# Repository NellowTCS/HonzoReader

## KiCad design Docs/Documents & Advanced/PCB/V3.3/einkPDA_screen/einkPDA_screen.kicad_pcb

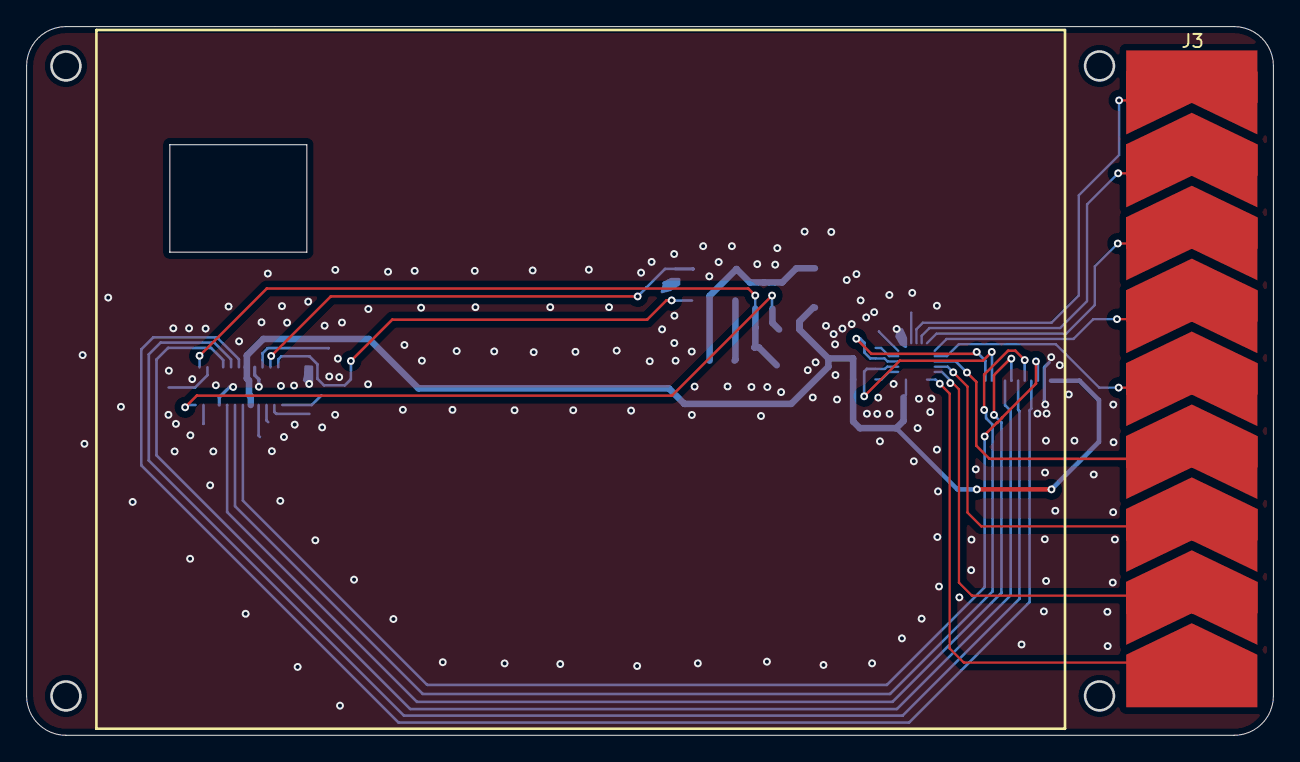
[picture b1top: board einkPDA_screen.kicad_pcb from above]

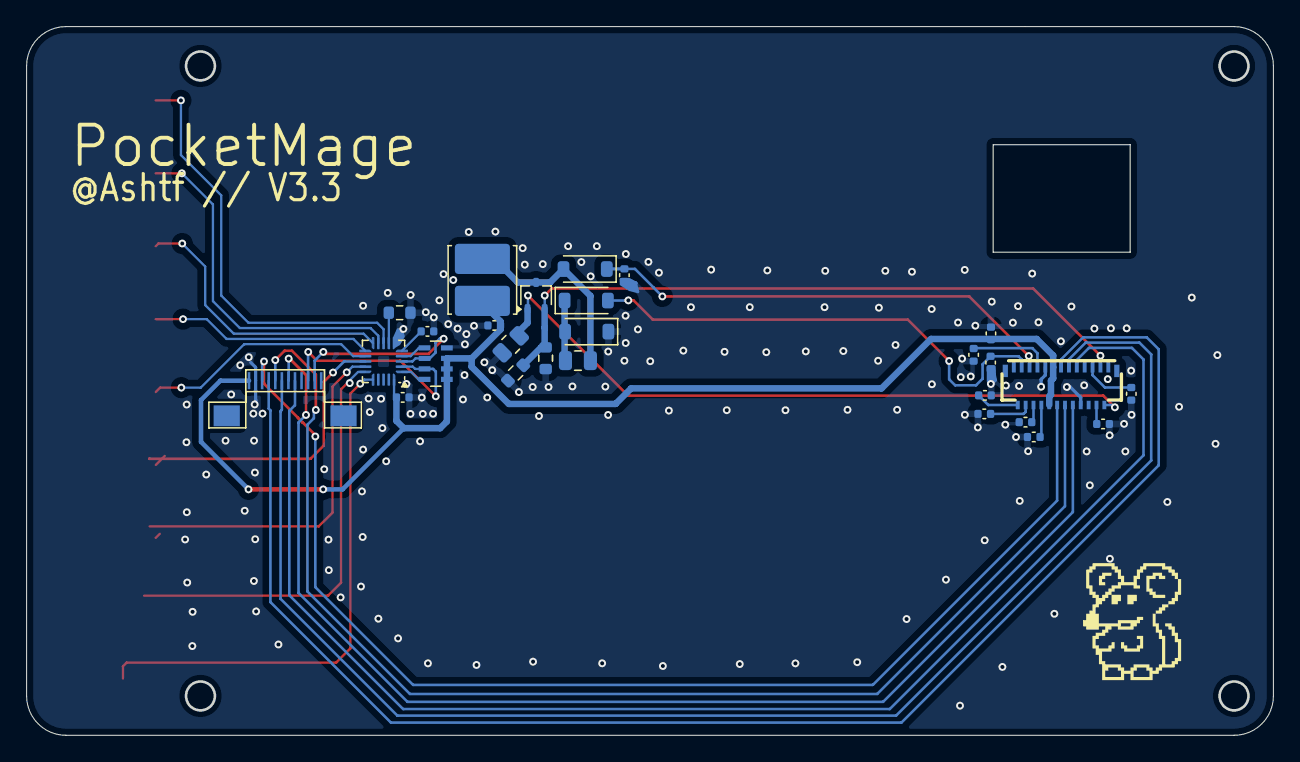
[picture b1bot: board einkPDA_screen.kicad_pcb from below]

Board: 2 copper layers, 95.0 x 54.0 mm, 28 parts (27 on the bottom side), 36 nets.

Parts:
C1, C3, C4, C5, C6, C7, C8, C9, C10: 1uF; C_0402_1005Metric
C2, C12: 4.7uF; C_0402_1005Metric
C11: 4.7uF; C_0805_2012Metric
C13, C14: 0.1uF; C_0402_1005Metric
D1, D2, D3: MBR0530; D_SOD-123
J2: AFE03-S25FMA-1H
J3: CapacitiveTouch; TouchSlider-9_50x10mm
J4: Conn_01x12_Pin; AFC01-S12FCA-00
L1: 10uH; L_Cenker_CKCS5020
Q1: Si1308EDL; SOT-323_SC-70
R1, R4: 1R; R_0603_1608Metric
R2: 10k; R_0805_2012Metric
R3: 75k; R_0603_1608Metric
RN1: 4x10k; R_Array_Concave_4x0603
U1: MPR121QR2; UQFN-20_3x3mm_P0.4mm

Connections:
+3.3V: C3.2, C12.1, C14.1, J2.15, J2.16, J4.1, L1.1, RN1.5 (R4.2), RN1.6 (R3.2), RN1.7 (R2.2), U1.20 (VDD)
/VCOM: C9.2, J2.24
BUSY: J2.9, J4.8
CS: J2.12, J4.5
D/C: J2.11, J4.6
GDR: J2.2, Q1.1 (G), R2.1
GND: C1.2, C2.1, C3.1, C4.1, C5.2, C6.1, C7.1, C8.2, C9.1, C10.1, C12.2, C13.2, C14.2, D2.1 (K), J2.8, J2.17, J4.2, R1.2, R2.2, R3.1, R4.2, RN1.8 (R1.2), U1.6 (VSS)
I2C_SCL: J4.10, RN1.3 (R3.1), U1.2 (SCL)
I2C_SDA: J4.11, RN1.2 (R2.1), U1.3 (SDA)
unnamed: C1.1, J2.4
unnamed: C2.2, J2.5
unnamed: C4.2, J2.18
unnamed: C5.1, J2.19
unnamed: C6.2, J2.20
unnamed: C7.2, J2.22
unnamed: C11.1, D1.1 (K), D2.2 (A)
unnamed: C11.2, D3.2 (A), L1.2, Q1.3 (D)
unnamed: J3.1, U1.8 (ELE0)
unnamed: J3.2, U1.9 (ELE1)
unnamed: J3.3, U1.10 (ELE2)
unnamed: J3.4, U1.11 (ELE3)
unnamed: J3.5, U1.12 (LED0/ELE4)
unnamed: J3.6, U1.13 (LED1/ELE5)
unnamed: J3.7, U1.14 (LED2/ELE6)
unnamed: J3.8, U1.15 (LED3/ELE7)
unnamed: J3.9, U1.16 (LED4/ELE8)
unnamed: RN1.1 (R1.1), U1.4 (ADDR)
unnamed: RN1.4 (R4.1), U1.1 (~IRQ)
unnamed: R3.2, U1.7 (REXT)
unnamed: C13.1, U1.5 (VREG)
PREVGH: C10.2, D3.1 (K), J2.21
PREVGL: C8.1, D1.2 (A), J2.23
RES: J2.10, J4.7
RESE: J2.3, Q1.2 (S), R1.1, R4.1
SCLK: J2.13, J4.4
SDI: J2.14, J4.3

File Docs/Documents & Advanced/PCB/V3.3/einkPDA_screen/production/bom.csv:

Designator,Footprint,Quantity,Value,LCSC Part #
"C1, C10, C3, C4, C5, C6, C7, C8, C9",0402,9,1uF,CL05A105KA5NQNC
C11,0805,1,4.7uF,CL21A475KAQNNNE
"C12, C2",0402,2,4.7uF,CL05A475MP5NRNC
"C13, C14",0402,2,0.1uF,CL05B104KO5NNNC
"D1, D2, D3",D_SOD-123,3,MBR0530,MBR0530
J2,AFE03-S25FMA-1H,1,~,AFE03-S25FMA-1H
J3,TouchSlider-9_50x10mm,1,CapacitiveTouch,
J4,AFC01-S12FCA-00,1,Conn_01x12_Pin,AFC01-S12FCA-00
L1,L_Cenker_CKCS5020,1,10uH,SWPA5020S100MT
Q1,SOT-323_SC-70,1,Si1308EDL,Si1308EDL
"R1, R4",0603,2,1R,0603WAF100KT5E
R2,0805,1,10k,0805W8F1002T5E
R3,0603,1,75k,0603WAF7502T5E
RN1,R_Array_Concave_4x0603,1,4x10k,4D03WGJ0103T5E
U1,UQFN-20_3x3mm_P0.4mm,1,MPR121QR2,MPR121QR2

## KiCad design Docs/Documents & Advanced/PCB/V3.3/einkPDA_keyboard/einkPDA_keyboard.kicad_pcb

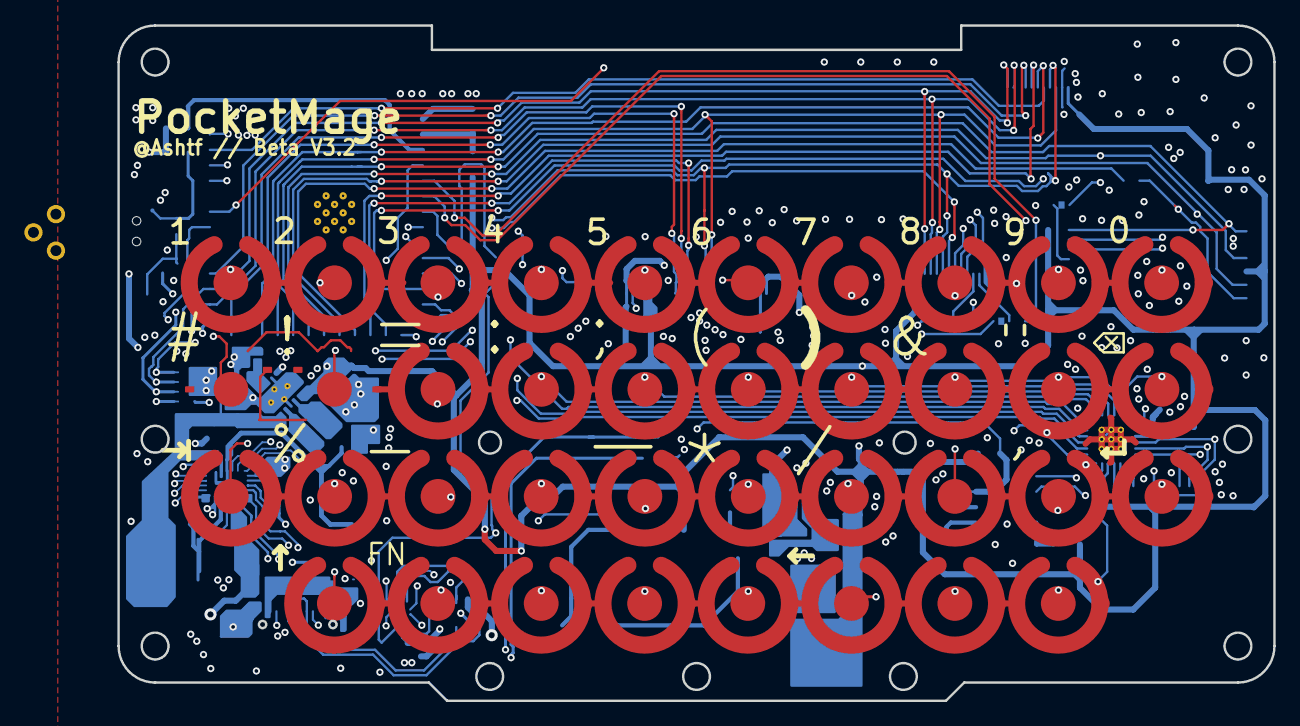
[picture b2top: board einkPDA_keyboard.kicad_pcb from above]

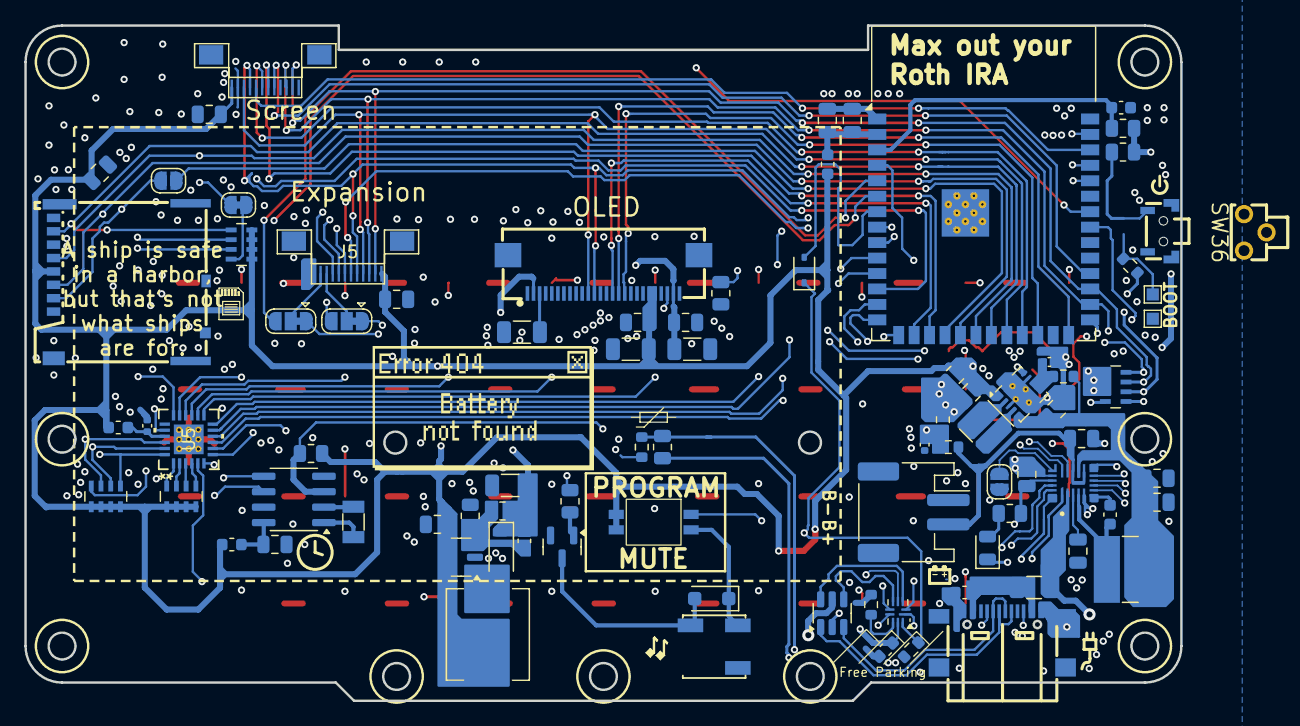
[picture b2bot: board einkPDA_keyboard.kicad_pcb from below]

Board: 4 copper layers, 95.0 x 55.5 mm, 125 parts (87 on the bottom side), 99 nets.

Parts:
BZ1: Buzzer; BUZ-SMD_3P_L5.0-W5.0-P3.50-TL
C1, C6, C20: 1uF; C_0603_1608Metric
C2, C9: 100nF; C_0805_2012Metric
C3, C21, C22: 22uF; C_0805_2012Metric
C7, C8, C19: 0.1uF; C_0402_1005Metric
C10, C23, C24, C26, C28, C29, C30, C31, C32: 10uF; C_0805_2012Metric
C11: 4.7pF; C_0603_1608Metric
C12, C13, C14, C16: 4.7uF; C_1206_3216Metric
C15, C17: .1uF; C_0805_2012Metric
C25: 4.7uF; C_0805_2012Metric
C27: 22nF; C_0603_1608Metric
D1: KT-0805Y; LED_0805_2012Metric
D2: MBR0530; D_SOD-123
D3: SM4007; D_SOD-123F
D5: D_Schottky; D_SOD-323
F1: SMD1206-500-6V; Fuse_1206_3216Metric
FB1, FB2, FB3: FerriteBead; L_0603_1608Metric
J1: USB_C_Receptacle_USB2.0_16P; USB-TYPE-C-SMD_TYPE-C-16P-QTWT
J2, J5: Conn_01x12_Pin; AFC01-S12FCA-00
J3: Conn_01x26_Pin; FPC-SMD_AFC24-S26FIA [DUAL-SIDE]
J4: Micro_SD_Card; TF-SMD_503398-1892
JP1, JP6: SolderJumper_2_Open; SolderJumper-2_P1.3mm_Open_RoundedPad1.0x1.5mm
JP3: SolderJumper_2_Bridged; SolderJumper-2_P1.3mm_Bridged_RoundedPad1.0x1.5mm
JP4, JP5: SolderJumper_3_Bridged12; SolderJumper-3_P1.3mm_Bridged12_RoundedPad1.0x1.5mm
L1: 10uH; L_Chilisin_BMRx00060630
L2: 1uH; L_Ferrocore_DLG-0504
L3: 2.2uH; L_Wurth_WE-LQSH-3012
Q1: MMBT3904; SOT-23
R1, R14: 10K; R_0805_2012Metric
R2, R8: 100R; R_0603_1608Metric
R3: 4.7k; R_0603_1608Metric
R6, R7: 100K; R_0603_1608Metric
R11, R16: 2k; R_0805_2012Metric
R12: 1.8M; R_0805_2012Metric
R13: 205k; R_0805_2012Metric
R15: 470R; R_0805_2012Metric
R17: 10k; R_0805_2012Metric
R18: 10k; R_0603_1608Metric
R20: 680k; R_0805_2012Metric
RN1, RN2, RN3, RN4: 4x10k; R_Array_Concave_4x0603
SW1, SW3, SW5, SW6, SW7, SW9, SW10, SW11, SW12, SW13, SW14, SW15, SW16, SW17, SW18, SW19, SW20, SW21, SW22, SW23, SW24, SW25, SW26, SW27, SW28, SW29, SW30, SW31, SW32, SW33, SW34, SW35, SW37, SW38, SW39, SW40: contact_pad_SINGLE
SW2: contactPad_cutoutR
SW4: SW_DIP_x02; 2X_DIP_DHN-02-V-TR
SW8: contactPad_cutoutL
SW36: YTS-C017-2B; KEY-TH_3P-L4.5-W4.5-P3.0-EH
SW43: EVQPUL02K; SW-SMD_TS24CA
TH1: NTC; R_0603_1608Metric
TP1, TP2: TestPoint; TestPoint_Pad_1.0x1.0mm
U1: ESP32-S3-WROOM-1
U2: USBLC6-2SC6; SOT-23-6
U3: TPS63001; Texas_DRC0010J_ThermalVias
U4: PCF8563T; SOIC-8_3.9x4.9mm_P1.27mm
U5: TCA8418RTWR; RTW24_2P45X2P45
U6: C2764211; JST_PH_2P_P2.00mm
U7: TPS61040DBV; SOT-23-5
U9: MP2722GRH-0000-Z; IC_MP2722GRH-0000-Z
U10: TS3USB30ERSWR; UQFN-10_1.4x1.8mm_P0.4mm
Y1: Crystal_32.768kHz; Crystal_SMD_3215-2Pin_3.2x1.5mm

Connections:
+3.3V: C6.2, C10.2, C16.1, C17.1, C21.2, C22.2, C24.1, C31.2, C32.2, FB1.1, FB2.2, FB3.1, J2.12, J3.21, J3.22, J4.4 (VDD), J5.1, L1.1, R1.1, R11.2, R14.1, RN1.1 (R1.1), RN1.2 (R2.1), RN1.3 (R3.1), RN1.4 (R4.1), RN2.5 (R4.2), RN2.6 (R3.2), RN2.7 (R2.2), RN2.8 (R1.2), RN3.1 (R1.1), RN3.2 (R2.1), RN3.3 (R3.1), RN3.4 (R4.1), RN4.5 (R4.2), RN4.6 (R3.2), RN4.7 (R2.2), SW4.1, SW4.2, U3.1 (VOUT), U3.10 (FB), U7.4 (EN), U7.5 (VIN), U10.9 (VCC)
+12V: C11.2, C12.1, C13.1, C15.1, D2.1 (K), J3.2, J3.25, R12.1
BAT+: C26.2, R6.1, U6.3 (BATT+), U9.12 (BATTSNS), U9.14 (BATT)
BAT_MEAS: C19.1, R6.2, R7.1, U1.4 (IO4)
BMS_INT: RN4.4 (R4.1), U1.33 (IO40), U9.8 (~INT)
BOOT: R8.1, R14.2, SW36.1, TP1.1
BUSY: J2.5, U1.30 (IO37)
BUZZER: R15.1, U1.10 (IO17)
BZ_CUTOFF: BZ1.1 (+), D3.1 (K), SW4.3
CS: J2.8, U1.38 (IO2)
D/C: J2.7, U1.23 (IO21)
EN: C1.2, R1.2, U1.3 (EN)
ESP_D+: U1.14 (IO20), U10.2 (D2+)
ESP_D-: U1.13 (IO19), U10.6 (D2-)
EX_A: J5.7, U1.15 (IO3)
EX_B: J5.8, U1.11 (IO18)
EX_C: J5.9, U1.34 (IO41)
EX_D: JP4.3 (B), U1.6 (IO6)
EX_E: JP5.3 (B), U1.5 (IO5)
GND: C1.1, C2.1, C3.1, C6.1, C7.2, C8.2, C9.1, C10.1, C12.2, C13.2, C14.2, C15.2, C16.2, C17.2, C19.2, C20.1, C21.1, C22.1, C23.1, C24.2, C25.2, C26.1, C28.1, C29.1, C30.1, C31.1, C32.1, J1.A1 (GND), J1.A12 (GND), J1.S1 (SHIELD), J2.11, J3.4, J3.5, J3.6, J3.7, J3.8, J3.9, J3.13, J3.14, J3.18, J3.19, J3.20, J3.23, J4.6 (VSS), J4.9 (SHIELD), J5.12, JP6.1 (A), Q1.2 (E), R3.2, R7.2, R13.2, R18.2, R20.2, SW36.2, SW36.3 (GND), SW43.4, TH1.2, TP2.1, U1.1 (GND), U1.40 (GND), U1.41 (GND), U2.2 (GND), U3.3 (PGND), U3.9 (GND), U3.11 (PGND), U4.4 (VSS), U5.19 (GND), U5.25 (EPAD), U6.1 (BATT-), U7.2 (GND), U9.5 (PGND), U9.18 (AGND), U10.4 (GND)
I2C_SCL: J2.3, J5.3, RN1.6 (R3.2), RN4.2 (R2.1), U1.28 (IO35), U4.6 (SCL), U5.23 (SCL), U9.16 (SCL)
I2C_SDA: J2.2, J5.2, RN1.7 (R2.2), RN4.3 (R3.1), U1.29 (IO36), U4.5 (SDA), U5.22 (SDA), U9.15 (SDA)
IC_D+: U9.21 (D+), U10.1 (D1+)
IC_D-: U9.20 (D-), U10.7 (D1-)
INT: RN1.5 (R4.2), U1.12 (IO8), U5.24 (*INT)
unnamed: BZ1.2 (-), D3.2 (A), Q1.3 (C)
unnamed: C20.2, F1.1, J1.A4 (VBUS), J1.A9 (VBUS)
unnamed: D1.2 (A), R16.1
unnamed: D1.1 (K), U9.11 (STAT/IB)
unnamed: D2.2 (A), L1.2, U7.1 (SW)
unnamed: D5.1 (K), R18.1, SW4.4, U10.10 (S)
unnamed: J1.A5 (CC1), U9.1 (CC1)
unnamed: J1.B5 (CC2), U9.22 (CC2)
unnamed: J1.A6 (D+), J1.B6 (D+), U2.1 (I/O1)
unnamed: J1.A7 (D-), J1.B7 (D-), U2.3 (I/O2)
unnamed: C14.1, J3.3
unnamed: J3.24, R20.1
unnamed: J4.2 (DAT3/CD), JP1.2 (B), RN3.7 (R2.2)
unnamed: J5.10, JP4.2 (C)
unnamed: J5.11, JP5.2 (C)
unnamed: JP3.2 (B), RN3.8 (R1.2)
unnamed: JP6.2 (B), U9.17 (~RST)
unnamed: Q1.1 (B), R15.2
unnamed: RN1.8 (R1.2), U5.20 (*RESET)
unnamed: RN2.1 (R1.1), U5.4 (ROW4)
unnamed: RN2.2 (R2.1), U5.3 (ROW5)
unnamed: RN2.3 (R3.1), U5.2 (ROW6)
unnamed: RN2.4 (R4.1), U5.1 (ROW7)
unnamed: RN4.1 (R1.1), U9.9 (PG/NTC2)
unnamed: C25.1, R16.2, RN4.8 (R1.2), U9.19 (VCC)
unnamed: C2.2, C3.2, FB1.2, U1.2 (3V3)
unnamed: R8.2, U1.27 (IO0)
unnamed: C7.1, R2.1, U3.6 (EN), U3.7 (PS/SYNC), U3.8 (VINA)
unnamed: L3.1, U3.4 (L1)
unnamed: L3.2, U3.2 (L2)
unnamed: U4.1 (OSCI), Y1.1
unnamed: U4.2 (OSCO), Y1.2
unnamed: C9.2, FB3.2, U4.8 (VDD)
unnamed: C8.1, FB2.1, U5.21 (VCC)
unnamed: C11.1, R12.2, R13.1, U7.3 (FB)
unnamed: C27.2, U9.6 (BST)
unnamed: R17.1, TH1.1, U9.10 (NTC1)
unnamed: C23.2, U9.3 (PMID)
unnamed: C27.1, L2.1, U9.4 (SW)
unnamed: R17.2, U9.7 (VRNTC)
unnamed: R3.1, U10.8 (~OE)
OLED_CS: J3.17, U1.24 (IO47)
OLED_D/C: J3.15, U1.16 (IO46)
OLED_RES: J3.16, U1.26 (IO45)
RES: J2.6, U1.17 (IO9)
RTC_INT: R11.1, U1.39 (IO1), U4.3 (~INT)
RX: JP5.1 (A), U1.36 (RXD0)
SD_CLK: J4.5 (CLK), JP3.1 (A), U1.20 (IO12)
SD_CMD: J4.3 (CMD), RN3.6 (R3.2), U1.19 (IO11)
SD_CS: JP1.1 (A), U1.18 (IO10)
SD_D0: J4.7 (DAT0), RN3.5 (R4.2), U1.21 (IO13)
SPI_MISO: J5.6, U1.9 (IO16)
SPI_MOSI: J2.10, J3.11, J5.4, U1.22 (IO14)
SPI_SCK: J2.9, J3.12, J5.5, U1.8 (IO15)
TX: JP4.1 (A), U1.37 (TXD0)
USB_5V: F1.2, U2.5 (VBUS), U9.2 (IN)
USB_D+: U2.6 (I/O1), U10.3 (D+)
USB_D-: U2.4 (I/O2), U10.5 (D-)
USB_SW: D5.2 (A), U1.7 (IO7)
V_SYS: C28.2, C29.2, C30.2, L2.2, R2.2, U3.5 (VIN), U9.13 (SYS)
col1: SW1.1, SW2.1, SW3.1, U5.9 (COL0)
col2: SW7.1, SW8.1, SW9.1, SW10.1, U5.10 (COL1)
col3: SW13.1, SW14.1, SW15.1, SW16.1, U5.11 (COL2)
col4: SW19.1, SW20.1, SW21.1, SW22.1, U5.12 (COL3)
col5: SW25.1, SW26.1, SW27.1, SW28.1, U5.13 (COL4)
col6: SW31.1, SW32.1, SW33.1, SW34.1, U5.14 (COL5)
col7: SW37.1, SW38.1, SW39.1, SW40.1, U5.15 (COL6)
col8: SW5.1, SW6.1, SW11.1, SW12.1, U5.16 (COL7)
col9: SW17.1, SW18.1, SW23.1, SW24.1, U5.17 (COL8)
col10: SW29.1, SW30.1, SW35.1, U5.18 (COL9)
row1: SW1.2, SW5.2, SW7.2, SW13.2, SW17.2, SW19.2, SW25.2, SW29.2, SW31.2, SW37.2, U5.8 (ROW0)
row2: SW2.2, SW6.2, SW8.2, SW14.2, SW18.2, SW20.2, SW26.2, SW30.2, SW32.2, SW38.2, U5.7 (ROW1)
row3: SW3.2, SW9.2, SW11.2, SW15.2, SW21.2, SW23.2, SW27.2, SW33.2, SW35.2, SW39.2, U5.6 (ROW2)
row4: SW10.2, SW12.2, SW16.2, SW22.2, SW24.2, SW28.2, SW34.2, SW40.2, U5.5 (ROW3)

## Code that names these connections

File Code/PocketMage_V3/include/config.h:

#ifndef CONFIG_H
#define CONFIG_H

// OTA App
// Is this an OTA APP? // OTA_APP: set -DOTA_APP_FLAG=1 in platformio.ini
#if OTA_APP_FLAG
#define OTA_APP true
#else
#define OTA_APP false
#endif

// CONFIGURATION & SETTINGS
////////////////////////////////////////////////////////////////////////////////////////////////////////////////////////////|
#define KB_COOLDOWN 3                           // Keypress cooldown
#define FULL_REFRESH_AFTER 5                    // Full refresh after N partial refreshes (CHANGE WITH CAUTION)
#define MAX_FILES 10                            // Number of files to store
#define FORMAT_SPIFFS_IF_FAILED true            // Format the SPIFFS filesystem if mount fails
#define SLEEPMODE "TEXT"                        // TEXT, SPLASH, CLOCK
#define TXT_APP_STYLE 1                         // 0: Old Style (NOT SUPPORTED), 1: New Style
#define SET_CLOCK_ON_UPLOAD false               // Should system clock be set automatically on code upload?
#define TOUCH_TIMEOUT_MS 1200                   // Delay after scrolling to return to typing mode (ms)
#define SYS_METADATA_FILE "/sys/SDMMC_META.txt" // File path to the file system metadata file
#define POWER_SAVE_FREQ 40                      // CPU freq for power save mode
#define IDLE_TIME 20000                         // time to wait for mage idle (ms)
////////////////////////////////////////////////////////////////////////////////////////////////////////////////////////////|

// PIN DEFINITION
#define I2C_SCL       35
#define I2C_SDA       36
#define MPR121_ADDR   0x5A
#define MP2722_ADDR   0x3F
#define USB_MUX_PIN   7

#define KB_IRQ        8
#define PWR_BTN       0 
#define BAT_SENS      4
#define CHRG_SENS     39
#define RTC_INT       1 

// SPI
#define SPI_MOSI      14
#define SPI_SCK       15

// OLED
#define OLED_CS       47
#define OLED_DC       46
#define OLED_RST      45

// E Ink
#define EPD_CS        2
#define EPD_DC        21
#define EPD_RST       9
#define EPD_BUSY      37

// SDMMC mode
#define SD_CLK        12
#define SD_CMD        11
#define SD_D0         13
#define SD_D1         5
#define SD_D2         6

// SDSPI mode
#define SD_CS         10
#define SD_MOSI       11
#define SD_SCK        12
#define SD_MISO       13

#define BZ_PIN        17

// ===================== SYSTEM SETTINGS =====================
// Persistent preferences
extern int TIMEOUT;              // Auto sleep timeout (seconds)
extern bool DEBUG_VERBOSE;       // Extra debug output
extern bool SYSTEM_CLOCK;        // Show clock on screen
extern bool SHOW_YEAR;           // Show year in clock
extern bool SAVE_POWER;          // Enable power saving mode
extern bool ALLOW_NO_MICROSD;    // Allow running without SD card
extern bool HOME_ON_BOOT;        // Start home app on boot
extern int OLED_BRIGHTNESS;      // OLED brightness (0-255)
extern int OLED_MAX_FPS;         // OLED max FPS
extern bool SD_SPI_COMPATIBILITY;

#endif

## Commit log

2026-02-16 WIP PCB updates
2026-03-05 Change ESP32 from N16R8 to N16
2026-03-12 Update PCB
2026-03-29 Polish apploader UX
2026-04-07 Update issue templates
2026-04-09 Implement hardware versioning
2026-04-09 Add terminal "exit" command
2026-04-13 PCB updates
2026-04-13 Fix webflasher manifest paths for legacy beta/production releases
2026-04-15 Fix line type labels in TXT.cpp
2026-04-23 Fix links to FAQ, Tutorials, and Command Manual
    Updated links in README to point to the new documentation site.
2026-04-26 Clarify OTA_APP build instructions in comments
    Updated comments for clarity on OTA_APP build instructions.
2026-04-28 Add terminal scrolling and linking
2026-04-30 Chat app WIP (not working)
2026-05-03 Improve slow full update system for prod boards
2026-05-25 Add "Echo" command to term
2026-06-14 Improvements
2026-06-16 IT WORKSSSSS
2026-06-16 CI and README
2026-06-16 Rebuild
2026-06-16 I'm a bit tired apparently /j [ci skip]
2026-06-16 One .gitignore
2026-06-17 Move Mesh-NOW submodule to lib/third_party
2026-06-17 Bump
2026-06-17 Sync manually
2026-06-19 chore: auto-build HonzoReader.tar
2026-06-20 Submodule bump
2026-06-21 Various bug fixes and improvements
